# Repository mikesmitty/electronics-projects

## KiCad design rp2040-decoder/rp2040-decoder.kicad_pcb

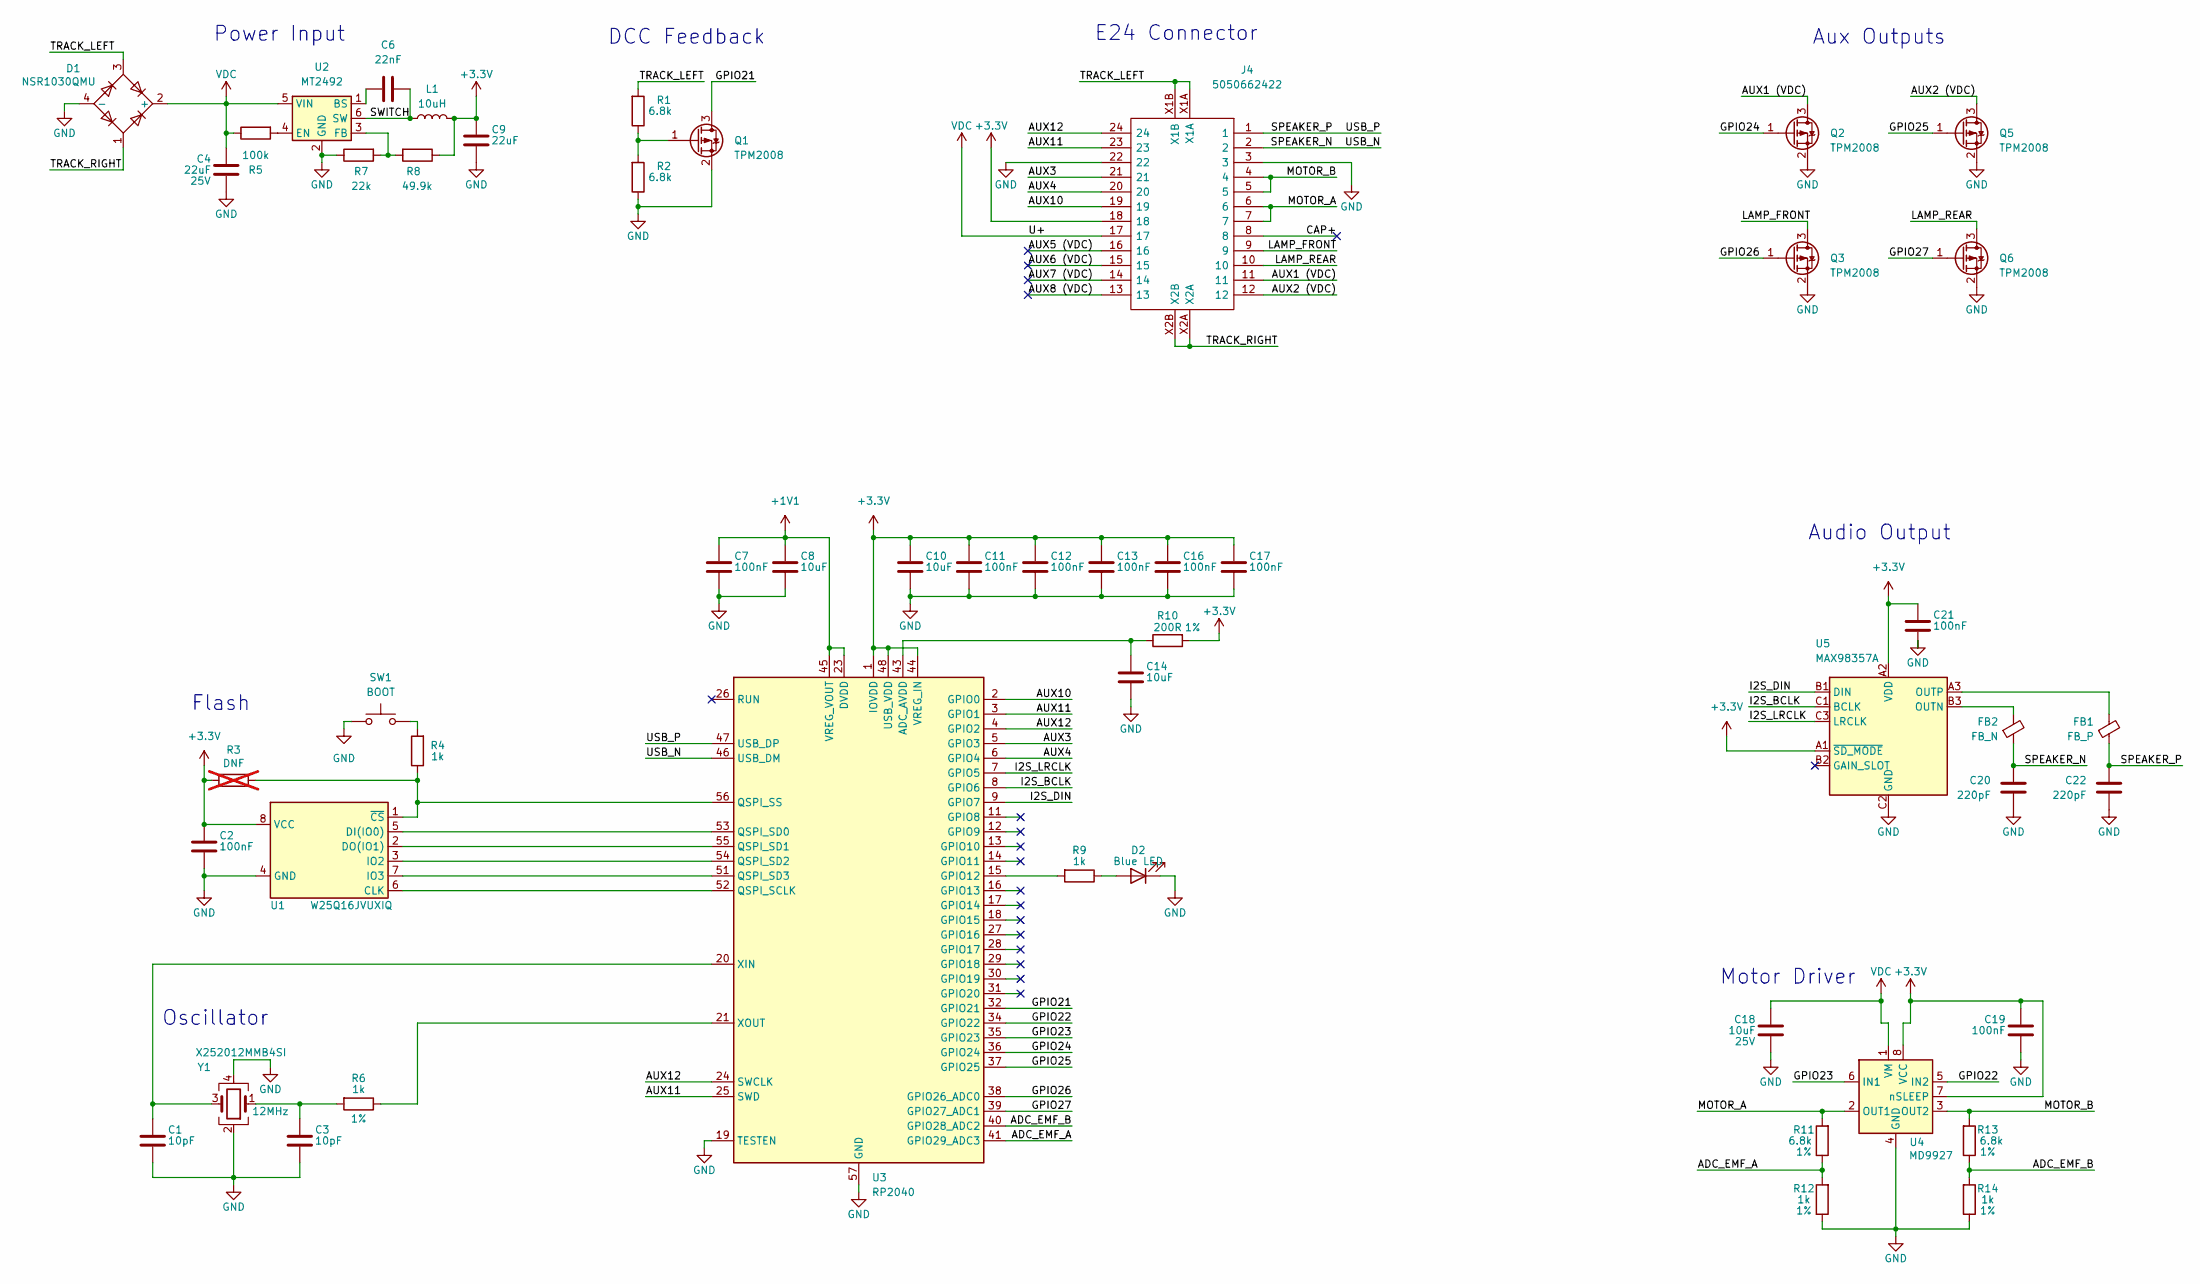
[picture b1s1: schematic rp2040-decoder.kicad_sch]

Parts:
C1, C3: 10pF; C_0201_0603Metric; Voltage 25V; LCSC C384956
C2, C11, C12, C13, C16, C17, C21: 100nF; C_0201_0603Metric; Voltage 6V3; LCSC C49062
C4: 22uF; CP_EIA-3528-21_Kemet-B; Voltage 25V; LCSC C2158664
C6: 22nF; C_0201_0603Metric; LCSC C76934
C7: 100nF; C_0201_0603Metric; Voltage 2V5; LCSC C49062
C8: 10uF; C_0402_1005Metric; Voltage 2V5; LCSC C15525
C9: 22uF; C_0603_1608Metric; LCSC C45783
C10, C14: 10uF; C_0402_1005Metric; Voltage 6V3; LCSC C15525
C18: 10uF; C_0603_1608Metric; Voltage 25V; LCSC C96446
C19: 100nF; C_0201_0603Metric; LCSC C49062
C20, C22: 220pF; C_0201_0603Metric; LCSC C62548
D1: NSR1030QMU; LCSC C889734
D2: Blue LED; LED_0402_1005Metric; LCSC C130724
FB1: FB_P; L_0402_1005Metric; LCSC C160973
FB2: FB_N; L_0402_1005Metric; LCSC C160973
J4: 5050662422; Manufacturer_Part_Number 505066-2422; LCSC C586118
L1: 10uH; L_1008_2520Metric; LCSC C5832376
Q1, Q2, Q3, Q5, Q6: TPM2008; Diodes_DFN1006-3; LCSC C2827633
R1, R2: 6.8k; R_0201_0603Metric; Tolerance 10%; LCSC C423451
R3: DNF; R_0402_1005Metric; not fitted
R4, R9: 1k; R_0201_0603Metric; Tolerance 10%; LCSC C270365
R5: 100k; R_0201_0603Metric; LCSC C270364
R6, R12, R14: 1k; R_0201_0603Metric; Tolerance 1%; LCSC C270365
R7: 22k; R_0201_0603Metric; LCSC C473469
R8: 49.9k; R_0201_0603Metric; LCSC C310169
R10: 200R; R_0201_0603Metric; Tolerance 1%; LCSC C270359
R11, R13: 6.8k; R_0201_0603Metric; Tolerance 1%; LCSC C423451
SW1: BOOT; Xunpu_TS-1088-AR02016; LCSC C720477
U1: W25Q16JVUXIQ; Winbond_USON-8-1EP_3x2mm_P0.5mm_EP0.2x1.6mm; LCSC C2843335
U2: MT2492; SOT-23-6; LCSC C89358
U3: RP2040; QFN-56-1EP_7x7mm_P0.4mm_EP3.2x3.2mm; LCSC C2040
U4: MD9927; DFN-8-1EP_2x2mm_P0.5mm_EP0.9x1.6mm; LCSC C2684662
U5: MAX98357A; Maxim_WLP-9_1.595x1.415_Layout3x3_P0.4mm_Ball0.27mm_Pad0.25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; LCSC C2682619
Y1: X252012MMB4SI; Crystal_SMD_2520-4Pin_2.5x2.0mm; LCSC C2896601

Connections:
+1V1: C7.1, C8.1, U3.23 (DVDD), U3.45 (VREG_VOUT), U3.50 (DVDD)
+3.3V: C2.1, C9.1, C10.1, C11.1, C12.1, C13.1, C16.1, C17.1, C19.1, C21.1, J4.18, L1.2, R3.2, R8.1, R10.1, U1.8 (VCC), U3.1 (IOVDD), U3.10 (IOVDD), U3.22 (IOVDD), U3.33 (IOVDD), U3.42 (IOVDD), U3.44 (VREG_IN), U3.48 (USB_VDD), U3.49 (IOVDD), U4.7 (nSLEEP), U4.8 (VCC), U5.A1 (~SD_MODE), U5.A2 (VDD)
/ADC_EMF_A: R11.1, R12.2, U3.41 (GPIO29_ADC3)
/ADC_EMF_B: R13.1, R14.2, U3.40 (GPIO28_ADC2)
/AUX1 (VDC): J4.11, Q2.3 (D)
/AUX2 (VDC): J4.12, Q5.3 (D)
/AUX3: J4.21, U3.5 (GPIO3)
/AUX4: J4.20, U3.6 (GPIO4)
/AUX5 (VDC): J4.16
/AUX6 (VDC): J4.15
/AUX7 (VDC): J4.14
/AUX8 (VDC): J4.13
/AUX10: J4.19, U3.2 (GPIO0)
/AUX11: J4.23, U3.3 (GPIO1), U3.25 (SWD)
/AUX12: J4.24, U3.4 (GPIO2), U3.24 (SWCLK)
/CAP+: J4.8
/GPIO21: Q1.3 (D), U3.32 (GPIO21)
/GPIO22: U3.34 (GPIO22), U4.5 (IN2)
/GPIO23: U3.35 (GPIO23), U4.6 (IN1)
/GPIO24: Q2.1 (G), U3.36 (GPIO24)
/GPIO25: Q5.1 (G), U3.37 (GPIO25)
/GPIO26: Q3.1 (G), U3.38 (GPIO26_ADC0)
/GPIO27: Q6.1 (G), U3.39 (GPIO27_ADC1)
/I2S_BCLK: U3.8 (GPIO6), U5.C1 (BCLK)
/I2S_DIN: U3.9 (GPIO7), U5.B1 (DIN)
/I2S_LRCLK: U3.7 (GPIO5), U5.C3 (LRCLK)
/LAMP_FRONT: J4.9, Q3.3 (D)
/LAMP_REAR: J4.10, Q6.3 (D)
/MOTOR_A: J4.6, J4.7, R11.2, U4.2 (OUT1)
/MOTOR_B: J4.4, J4.5, R13.2, U4.3 (OUT2)
/SPEAKER_N: C20.1, FB2.1, J4.2, U3.46 (USB_DM)
/SPEAKER_P: C22.1, FB1.1, J4.1, U3.47 (USB_DP)
/SWITCH: C6.2, L1.1, U2.6 (SW)
/TRACK_LEFT: D1.3, J4.X1A, J4.X1B, R1.2
/TRACK_RIGHT: D1.1, J4.X2A, J4.X2B
GND: C1.2, C2.2, C3.2, C4.2, C7.2, C8.2, C9.2, C10.2, C11.2, C12.2, C13.2, C14.2, C16.2, C17.2, C18.2, C19.2, C20.2, C21.2, C22.2, D1.4 (-), D2.1 (K), J4.3, J4.22, Q1.2 (S), Q2.2 (S), Q3.2 (S), Q5.2 (S), Q6.2 (S), R2.1, R7.1, R12.1, R14.1, SW1.1, U1.4 (GND), U1.9 (GND), U2.2 (GND), U3.19 (TESTEN), U3.57 (GND), U4.4 (GND), U4.9 (GND), U5.C2 (GND), Y1.2, Y1.4
unnamed: C3.1, R6.2, Y1.1
unnamed: D2.2 (A), R9.1
unnamed: Q1.1 (G), R1.1, R2.2
unnamed: R4.2, SW1.2
unnamed: U1.6 (CLK), U3.52 (QSPI_SCLK)
unnamed: U1.5 (DI(IO0)), U3.53 (QSPI_SD0)
unnamed: U1.2 (DO(IO1)), U3.55 (QSPI_SD1)
unnamed: U1.3 (IO2), U3.54 (QSPI_SD2)
unnamed: U1.7 (IO3), U3.51 (QSPI_SD3)
unnamed: R3.1, R4.1, U1.1 (~CS), U3.56 (QSPI_SS)
unnamed: C6.1, U2.1 (BS)
unnamed: R5.2, U2.4 (EN)
unnamed: R7.2, R8.2, U2.3 (FB)
unnamed: C14.1, R10.2, U3.43 (ADC_AVDD)
unnamed: R9.2, U3.15 (GPIO12)
unnamed: C1.1, U3.20 (XIN), Y1.3
unnamed: R6.1, U3.21 (XOUT)
unnamed: FB2.2, U5.B3 (OUTN)
unnamed: FB1.2, U5.A3 (OUTP)
VDC: C4.1, C18.1, D1.2 (+), J4.17, R5.1, U2.5 (VIN), U4.1 (VM)

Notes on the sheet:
Aux Outputs
Motor Driver
Oscillator
Power Input
Flash
Audio Output
E24 Connector
DCC Feedback

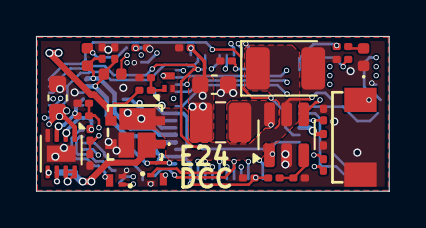
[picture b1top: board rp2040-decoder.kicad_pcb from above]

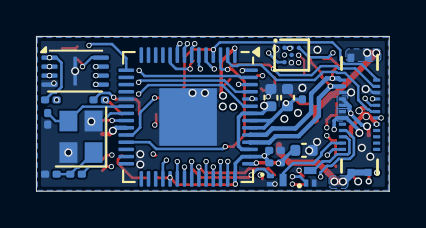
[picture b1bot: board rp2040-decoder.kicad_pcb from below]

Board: 4 copper layers, 19.6 x 8.6 mm, 51 parts (18 on the bottom side), 51 nets.

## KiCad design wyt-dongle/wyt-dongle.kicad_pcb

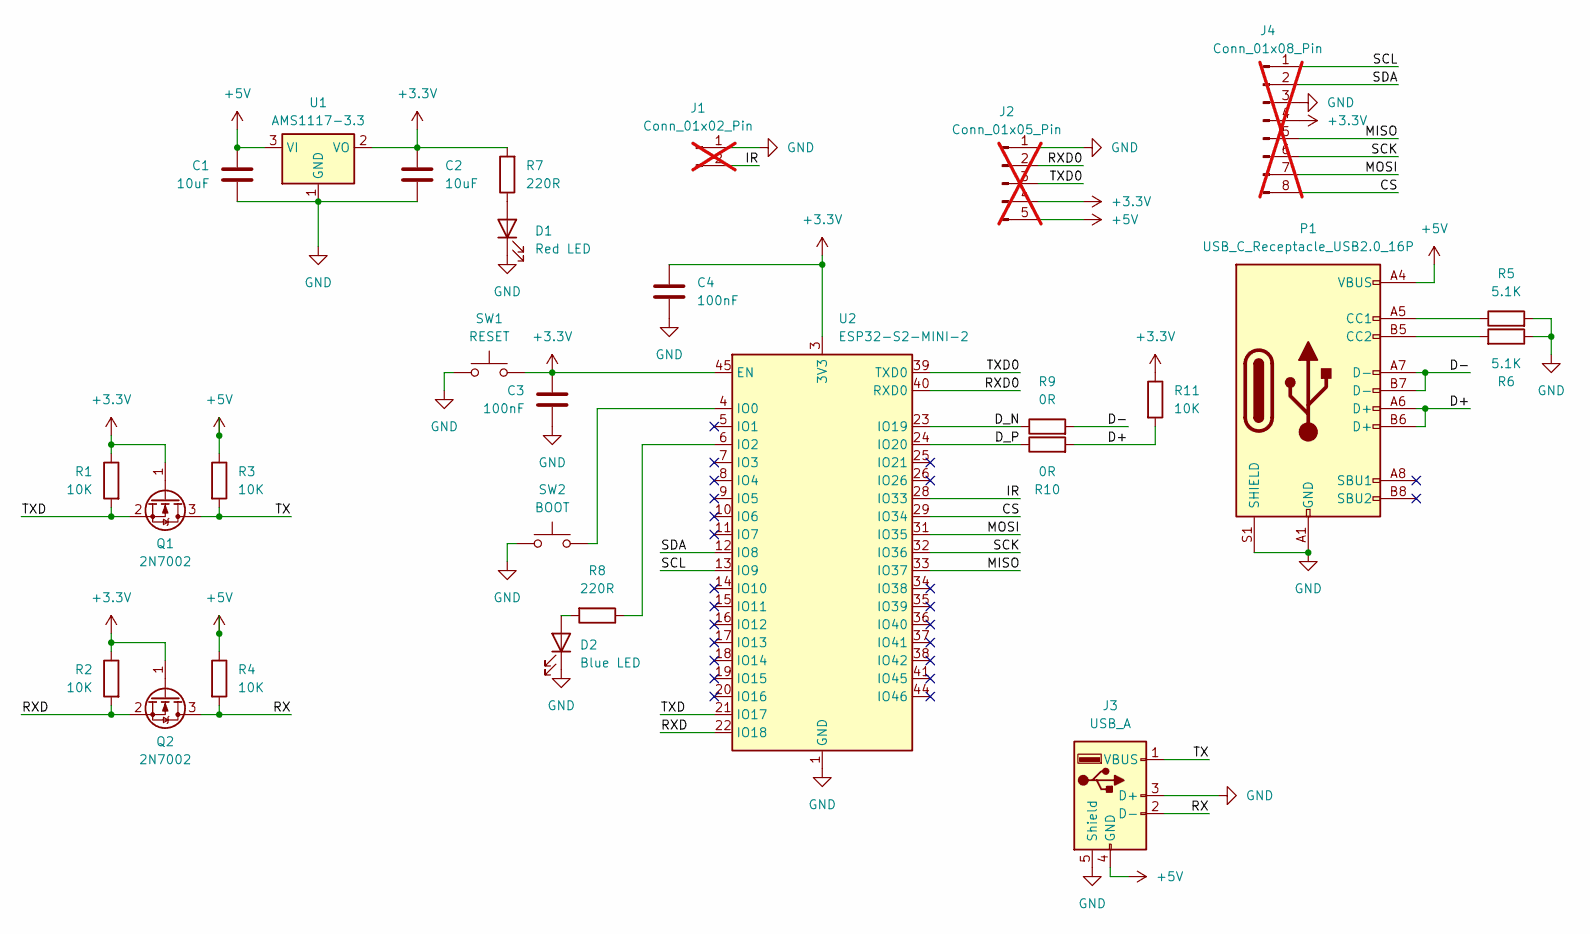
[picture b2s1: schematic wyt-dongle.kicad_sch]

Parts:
C1, C2: 10uF; C_0402_1005Metric; LCSC C15525
C3, C4: 100nF; C_0402_1005Metric; LCSC C1525
D1: Red LED; LED_0603_1608Metric; LCSC C2286
D2: Blue LED; LED_0603_1608Metric; LCSC C2288
J1: Conn_01x02_Pin; PinHeader_1x02_P2.54mm_Vertical; not fitted
J2: Conn_01x05_Pin; 1x05_Header_Pins_Horizontal; not fitted
J3: USB_A; USB_A_PLUG_JING; LCSC C9739
J4: Conn_01x08_Pin; 1x08_Header_Pins_Horizontal; not fitted
P1: USB_C_Receptacle_USB2.0_16P; USB_C_Receptacle_GCT_USB4105-xx-A_16P_TopMnt_Horizontal; LCSC C2765186
Q1, Q2: 2N7002; SOT-23; LCSC C8545
R1, R2, R3, R4, R11: 10K; R_0402_1005Metric; LCSC C25744
R5, R6: 5.1K; R_0402_1005Metric; LCSC C25905
R7, R8: 220R; R_0402_1005Metric; LCSC C25091
R9, R10: 0R; R_0402_1005Metric; LCSC C17168
SW1: RESET; Xunpu_TS-1088-AR02016; LCSC C720477
SW2: BOOT; Xunpu_TS-1088-AR02016; LCSC C720477
U1: AMS1117-3.3; SOT-223-3_TabPin2; LCSC C6186
U2: ESP32-S2-MINI-2; ESP32-MINI-1; LCSC C3013908

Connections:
+3.3V: C2.1, C3.2, C4.1, J2.4, J4.4, Q1.1 (G), Q2.1 (G), R1.1, R2.1, R7.2, R11.1, SW1.2, U1.2 (VO), U2.3 (3V3), U2.45 (EN)
+5V: C1.1, J2.5, J3.4 (GND), P1.A4 (VBUS), P1.A9 (VBUS), P1.B4 (VBUS), P1.B9 (VBUS), R3.1, R4.1, U1.3 (VI)
/CS: J4.8, U2.29 (IO34)
/D+: P1.A6 (D+), P1.B6 (D+), R10.2, R11.2
/D-: P1.A7 (D-), P1.B7 (D-), R9.2
/D_N: R9.1, U2.23 (IO19)
/D_P: R10.1, U2.24 (IO20)
/IR: J1.2, U2.28 (IO33)
/MISO: J4.5, U2.33 (IO37)
/MOSI: J4.7, U2.31 (IO35)
/RX: J3.2 (D-), Q2.3 (D), R4.2
/RXD: Q2.2 (S), R2.2, U2.22 (IO18)
/RXD0: J2.2, U2.40 (RXD0)
/SCK: J4.6, U2.32 (IO36)
/SCL: J4.1, U2.13 (IO9)
/SDA: J4.2, U2.12 (IO8)
/TX: J3.1 (VBUS), Q1.3 (D), R3.2
/TXD: Q1.2 (S), R1.2, U2.21 (IO17)
/TXD0: J2.3, U2.39 (TXD0)
GND: C1.2, C2.2, C3.1, C4.2, D1.1 (K), D2.1 (K), J1.1, J2.1, J3.3 (D+), J3.5 (Shield), J4.3, P1.A1 (GND), P1.A12 (GND), P1.B1 (GND), P1.B12 (GND), P1.S1 (SHIELD), R5.2, R6.1, SW1.1, SW2.1, U1.1 (GND), U2.1 (GND), U2.2 (GND), U2.30 (GND), U2.42 (GND), U2.43 (GND), U2.46 (GND), U2.47 (GND), U2.48 (GND), U2.49 (GND), U2.50 (GND), U2.51 (GND), U2.52 (GND), U2.53 (GND), U2.54 (GND), U2.55 (GND), U2.56 (GND), U2.57 (GND), U2.58 (GND), U2.59 (GND), U2.60 (GND), U2.61 (GND), U2.62 (GND), U2.63 (GND), U2.64 (GND), U2.65 (GND), U2.66 (GND), U2.67 (GND), U2.68 (GND), U2.69 (GND), U2.70 (GND), U2.71 (GND), U2.72 (GND), U2.73 (GND)
unnamed: D1.2 (A), R7.1
unnamed: D2.2 (A), R8.2
unnamed: P1.A5 (CC1), R5.1
unnamed: P1.B5 (CC2), R6.2
unnamed: SW2.2, U2.4 (IO0)
unnamed: R8.1, U2.6 (IO2)

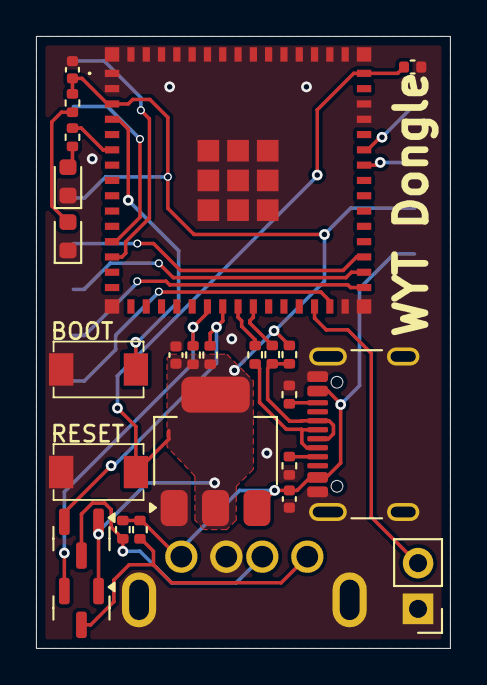
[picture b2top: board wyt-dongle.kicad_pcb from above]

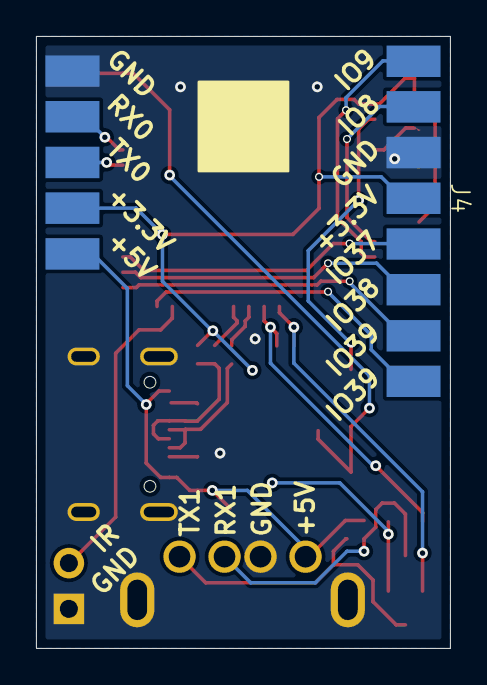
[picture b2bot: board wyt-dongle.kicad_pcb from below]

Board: 2 copper layers, 23.0 x 34.0 mm, 28 parts (2 on the bottom side), 26 nets.

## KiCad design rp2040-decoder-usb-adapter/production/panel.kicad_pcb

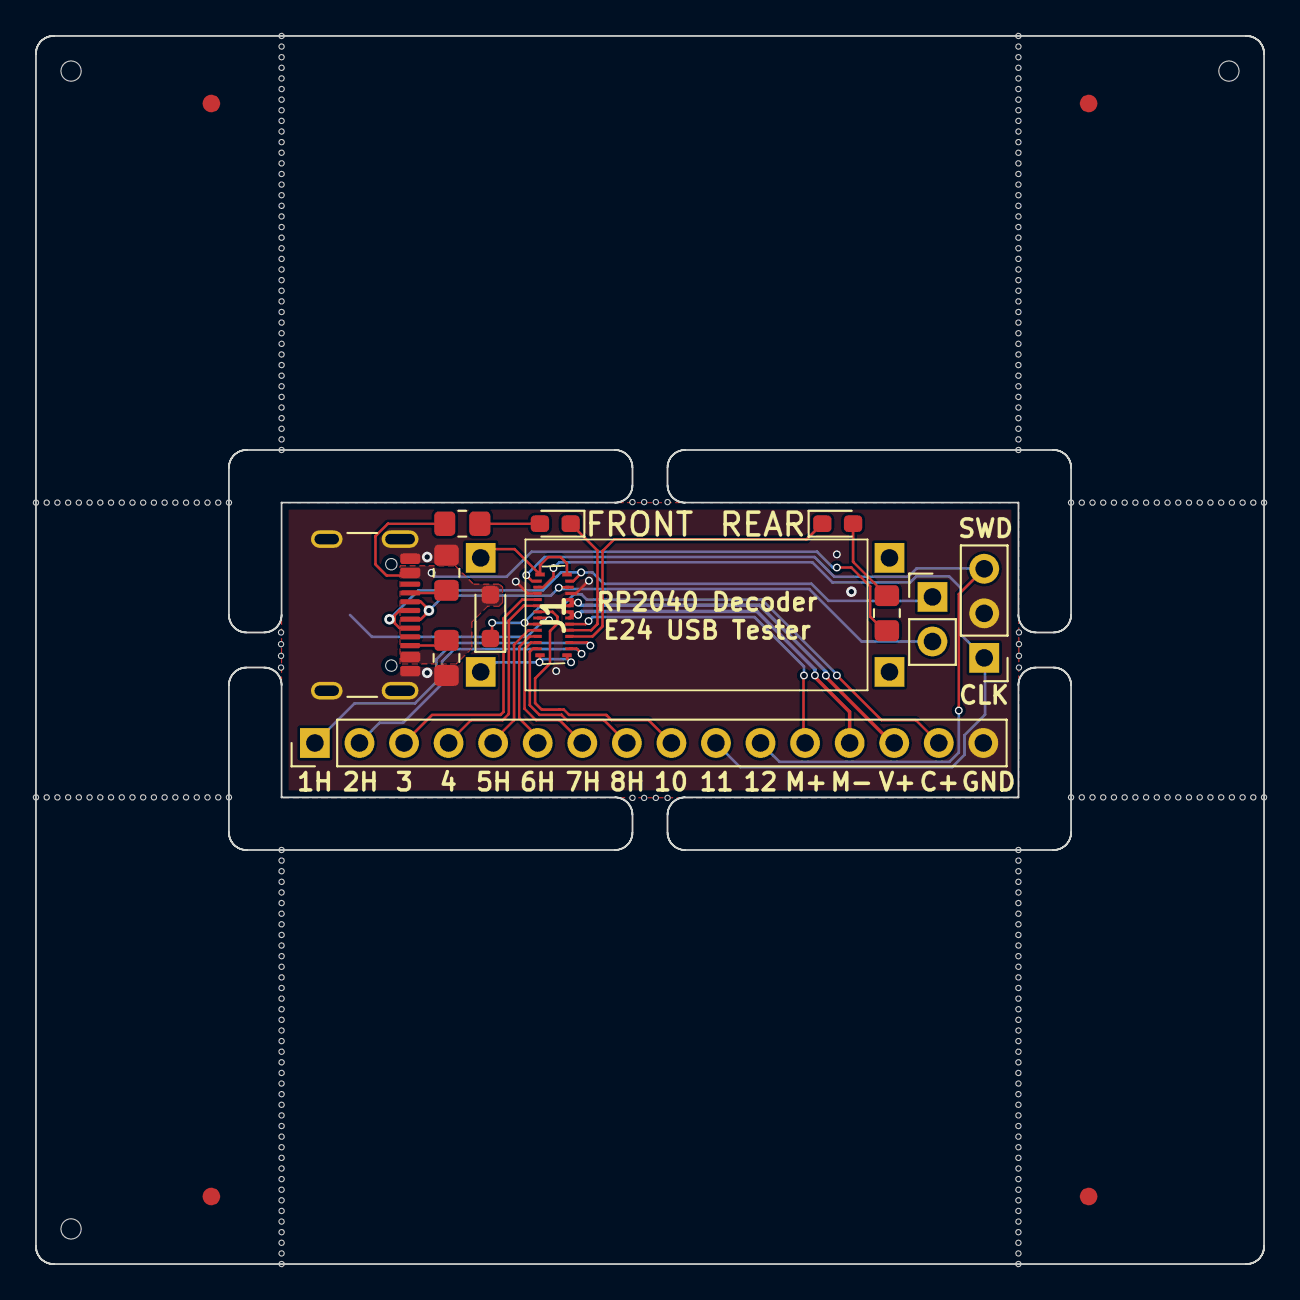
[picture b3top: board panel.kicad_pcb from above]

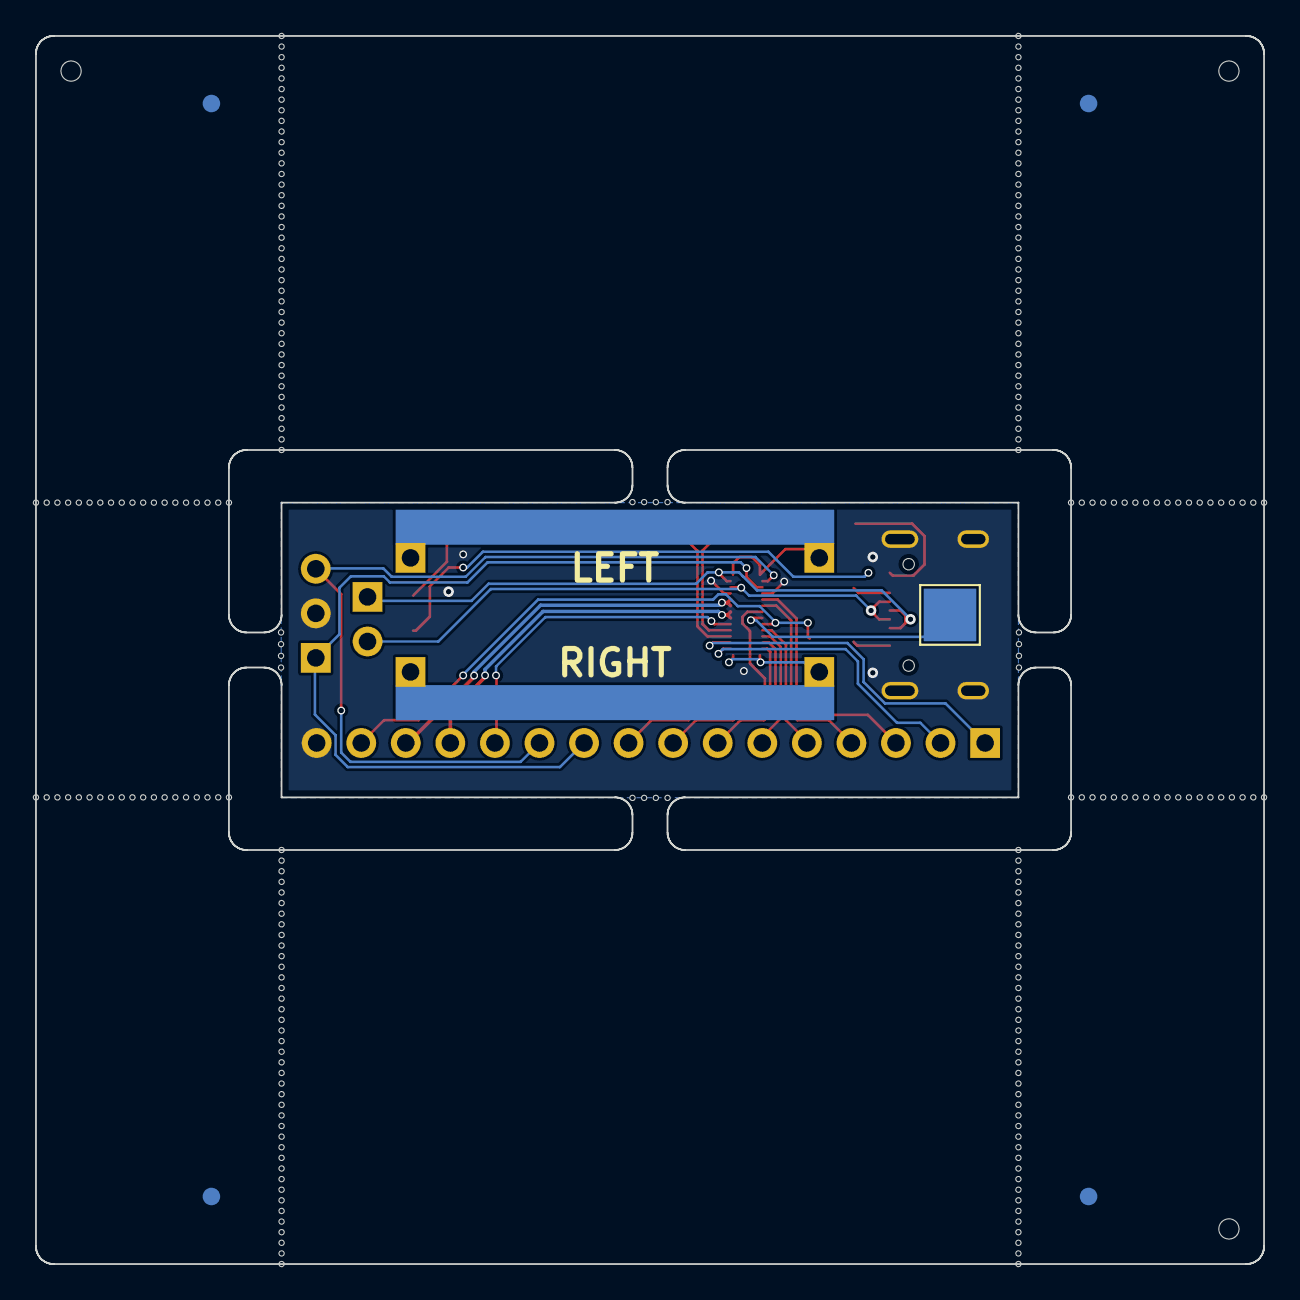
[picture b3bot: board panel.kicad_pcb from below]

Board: 2 copper layers, 70.0 x 70.0 mm, 277 parts (6 on the bottom side), 28 nets.

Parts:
D1: Backflow Diode; D_SOD-323_HandSoldering
D2: LAMP_FRONT; LED_0603_1608Metric_Pad1.05x0.95mm_HandSolder
D3: LAMP_REAR; LED_0603_1608Metric_Pad1.05x0.95mm_HandSolder
J1: 505070-2422; 5050702422
J2: SWD; PinHeader_1x03_P2.54mm_Vertical
J3: SPEAKER; PinHeader_1x02_P2.54mm_Vertical
J4: MISC1; PinHeader_1x16_P2.54mm_Vertical
J8: RAIL_PADS; N_Gauge_Rail
KiKit_FID_B_1, KiKit_FID_B_2, KiKit_FID_B_3, KiKit_FID_B_4: Fiducial
KiKit_FID_T_1, KiKit_FID_T_2, KiKit_FID_T_3, KiKit_FID_T_4: Fiducial
KiKit_MB_1_1, KiKit_MB_1_2, KiKit_MB_1_3, KiKit_MB_1_4, KiKit_MB_2_1, KiKit_MB_2_2, KiKit_MB_2_3, KiKit_MB_2_4, KiKit_MB_3_1, KiKit_MB_3_2, KiKit_MB_3_3, KiKit_MB_3_4, KiKit_MB_4_1, KiKit_MB_4_2, KiKit_MB_4_3, KiKit_MB_4_4, KiKit_MB_5_1, KiKit_MB_5_2, KiKit_MB_5_3, KiKit_MB_5_4, KiKit_MB_5_5, KiKit_MB_5_6, KiKit_MB_5_7, KiKit_MB_5_8, KiKit_MB_5_9, KiKit_MB_5_10, KiKit_MB_5_11, KiKit_MB_5_12, KiKit_MB_5_13, KiKit_MB_5_14, KiKit_MB_5_15, KiKit_MB_5_16, KiKit_MB_5_17, KiKit_MB_5_18, KiKit_MB_5_19, KiKit_MB_5_20, KiKit_MB_5_21, KiKit_MB_5_22, KiKit_MB_5_23, KiKit_MB_5_24, KiKit_MB_5_25, KiKit_MB_5_26, KiKit_MB_5_27, KiKit_MB_5_28, KiKit_MB_5_29, KiKit_MB_5_30, KiKit_MB_5_31, KiKit_MB_5_32, KiKit_MB_5_33, KiKit_MB_5_34, KiKit_MB_5_35, KiKit_MB_5_36, KiKit_MB_5_37, KiKit_MB_5_38, KiKit_MB_5_39, KiKit_MB_5_40, KiKit_MB_6_1, KiKit_MB_6_2, KiKit_MB_6_3, KiKit_MB_6_4, KiKit_MB_6_5, KiKit_MB_6_6, KiKit_MB_6_7, KiKit_MB_6_8, KiKit_MB_6_9, KiKit_MB_6_10, KiKit_MB_6_11, KiKit_MB_6_12, KiKit_MB_6_13, KiKit_MB_6_14, KiKit_MB_6_15, KiKit_MB_6_16, KiKit_MB_6_17, KiKit_MB_6_18, KiKit_MB_6_19, KiKit_MB_6_20, KiKit_MB_6_21, KiKit_MB_6_22, KiKit_MB_6_23, KiKit_MB_6_24, KiKit_MB_6_25, KiKit_MB_6_26, KiKit_MB_6_27, KiKit_MB_6_28, KiKit_MB_6_29, KiKit_MB_6_30, KiKit_MB_6_31, KiKit_MB_6_32, KiKit_MB_6_33, KiKit_MB_6_34, KiKit_MB_6_35, KiKit_MB_6_36, KiKit_MB_6_37, KiKit_MB_6_38, KiKit_MB_6_39, KiKit_MB_6_40, KiKit_MB_7_1, KiKit_MB_7_2, KiKit_MB_7_3, KiKit_MB_7_4, KiKit_MB_7_5, KiKit_MB_7_6, KiKit_MB_7_7, KiKit_MB_7_8, KiKit_MB_7_9, KiKit_MB_7_10, KiKit_MB_7_11, KiKit_MB_7_12, KiKit_MB_7_13, KiKit_MB_7_14, KiKit_MB_7_15, KiKit_MB_7_16, KiKit_MB_7_17, KiKit_MB_7_18, KiKit_MB_7_19, KiKit_MB_7_20, KiKit_MB_7_21, KiKit_MB_7_22, KiKit_MB_7_23, KiKit_MB_7_24, KiKit_MB_7_25, KiKit_MB_7_26, KiKit_MB_7_27, KiKit_MB_7_28, KiKit_MB_7_29, KiKit_MB_7_30, KiKit_MB_7_31, KiKit_MB_7_32, KiKit_MB_7_33, KiKit_MB_7_34, KiKit_MB_7_35, KiKit_MB_7_36, KiKit_MB_7_37, KiKit_MB_7_38, KiKit_MB_7_39, KiKit_MB_7_40, KiKit_MB_8_1, KiKit_MB_8_2, KiKit_MB_8_3, KiKit_MB_8_4, KiKit_MB_8_5, KiKit_MB_8_6, KiKit_MB_8_7, KiKit_MB_8_8, KiKit_MB_8_9, KiKit_MB_8_10, KiKit_MB_8_11, KiKit_MB_8_12, KiKit_MB_8_13, KiKit_MB_8_14, KiKit_MB_8_15, KiKit_MB_8_16, KiKit_MB_8_17, KiKit_MB_8_18, KiKit_MB_8_19, KiKit_MB_8_20, KiKit_MB_8_21, KiKit_MB_8_22, KiKit_MB_8_23, KiKit_MB_8_24, KiKit_MB_8_25, KiKit_MB_8_26, KiKit_MB_8_27, KiKit_MB_8_28, KiKit_MB_8_29, KiKit_MB_8_30, KiKit_MB_8_31, KiKit_MB_8_32, KiKit_MB_8_33, KiKit_MB_8_34, KiKit_MB_8_35, KiKit_MB_8_36, KiKit_MB_8_37, KiKit_MB_8_38, KiKit_MB_8_39, KiKit_MB_8_40, KiKit_MB_9_1, KiKit_MB_9_2, KiKit_MB_9_3, KiKit_MB_9_4, KiKit_MB_9_5, KiKit_MB_9_6, KiKit_MB_9_7, KiKit_MB_9_8, KiKit_MB_9_9, KiKit_MB_9_10, KiKit_MB_9_11, KiKit_MB_9_12, KiKit_MB_9_13, KiKit_MB_9_14, KiKit_MB_9_15, KiKit_MB_9_16, KiKit_MB_9_17, KiKit_MB_9_18, KiKit_MB_9_19, KiKit_MB_10_1, KiKit_MB_10_2, KiKit_MB_10_3, KiKit_MB_10_4, KiKit_MB_10_5, KiKit_MB_10_6, KiKit_MB_10_7, KiKit_MB_10_8, KiKit_MB_10_9, KiKit_MB_10_10, KiKit_MB_10_11, KiKit_MB_10_12, KiKit_MB_10_13, KiKit_MB_10_14, KiKit_MB_10_15, KiKit_MB_10_16, KiKit_MB_10_17, KiKit_MB_10_18, KiKit_MB_10_19, KiKit_MB_11_1, KiKit_MB_11_2, KiKit_MB_11_3, KiKit_MB_11_4, KiKit_MB_11_5, KiKit_MB_11_6, KiKit_MB_11_7, KiKit_MB_11_8, KiKit_MB_11_9, KiKit_MB_11_10, KiKit_MB_11_11, KiKit_MB_11_12, KiKit_MB_11_13, KiKit_MB_11_14, KiKit_MB_11_15, KiKit_MB_11_16, KiKit_MB_11_17, KiKit_MB_11_18, KiKit_MB_11_19, KiKit_MB_12_1, KiKit_MB_12_2, KiKit_MB_12_3, KiKit_MB_12_4, KiKit_MB_12_5, KiKit_MB_12_6, KiKit_MB_12_7, KiKit_MB_12_8, KiKit_MB_12_9, KiKit_MB_12_10, KiKit_MB_12_11, KiKit_MB_12_12, KiKit_MB_12_13, KiKit_MB_12_14, KiKit_MB_12_15, KiKit_MB_12_16, KiKit_MB_12_17, KiKit_MB_12_18, KiKit_MB_12_19: NPTH
KiKit_TO_1, KiKit_TO_2, KiKit_TO_3: NPTH
P1: USB_C_Receptacle_USB2.0_16P; USB_C_Receptacle_GCT_USB4105-xx-A_16P_TopMnt_Horizontal
R1, R2: 5.1K; R_0805_2012Metric_Pad1.20x1.40mm_HandSolder
R3, R4: 220R; R_0805_2012Metric_Pad1.20x1.40mm_HandSolder
TP1: VCC; TestPoint_Pad_3.0x3.0mm

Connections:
Board_0-+5V: D1.2 (A), P1.A4 (VBUS), P1.A9 (VBUS), P1.B4 (VBUS), P1.B9 (VBUS), R3.1, R4.1
Board_0-/AUX1 (VDC): J1.11, J4.1
Board_0-/AUX2 (VDC): J1.12, J4.2
Board_0-/AUX3: J1.21, J4.3
Board_0-/AUX4: J1.20, J4.4
Board_0-/AUX5 (VDC): J1.16, J4.5
Board_0-/AUX6 (VDC): J1.15, J4.6
Board_0-/AUX7 (VDC): J1.14, J4.7
Board_0-/AUX8 (VDC): J1.13, J4.8
Board_0-/AUX10: J1.19, J4.9
Board_0-/AUX11: J1.23, J2.1, J4.10
Board_0-/AUX12: J1.24, J2.3, J4.11
Board_0-/CAP+: J1.8, J4.12
Board_0-/D+: J1.1, J3.1, P1.A6 (D+), P1.B6 (D+)
Board_0-/D-: J1.2, J3.2, P1.A7 (D-), P1.B7 (D-)
Board_0-/LAMP_FRONT: D2.1 (K), J1.9
Board_0-/LAMP_REAR: D3.1 (K), J1.10
Board_0-/MOTOR_A: J1.6, J1.7, J4.13
Board_0-/MOTOR_B: J1.4, J1.5, J4.14
Board_0-/TRACK_LEFT: J1.X1A, J1.X1B, J8.1
Board_0-/TRACK_RIGHT: J1.X2A, J1.X2B, J8.2
Board_0-GND: J1.3, J1.22, J2.2, J4.16, P1.A1 (GND), P1.A12 (GND), P1.B1 (GND), P1.B12 (GND), P1.S1 (SHIELD), R1.2, R2.1
Board_0-Net-(D2-A): D2.2 (A), R3.2
Board_0-Net-(D3-A): D3.2 (A), R4.2
Board_0-Net-(P1-CC1): P1.A5 (CC1), R1.1
Board_0-Net-(P1-CC2): P1.B5 (CC2), R2.2
Board_0-VCC: J1.18, TP1.1
Board_0-VDC: D1.1 (K), J1.17, J4.15

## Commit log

2024-11-29 chore: add gitignore for kicad projects
2024-11-29 feat: add initial dongle design
2024-12-11 feat: expose more gpios and add reset button
    fix: switch to larger LDO
    fix: avoid gpio tied to flash for IR LED
    fix: connect all usb data pins
    fix: add 5.1K resistors for passive usb power
2024-12-18 chore: space buttons apart for easier flashing
2025-01-11 feat: add rp2040 e24 decoder and accessories
2025-06-17 chore: add missing csv files
